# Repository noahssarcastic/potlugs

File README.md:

# potlugs
16mm panel-mount potentiometer wiring adaptor board.

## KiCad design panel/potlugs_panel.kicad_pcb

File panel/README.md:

# potlugs_panel

## Panelize (kikit)

```
kikit panelize ^
    --layout "grid; rows: 6; cols: 4; space: 2mm; rotation: 90deg" ^
    --tabs "fixed; width: 3mm; vcount: 1" ^
    --cuts "mousebites; drill: 0.5mm; spacing: 1mm; offset: 0.2mm; prolong: 0.5mm" ^
    --framing "frame; width: 5mm; space: 3mm; mintotalheight: 75mm; mintotalwidth: 75mm" ^
    --post "millradius: 1mm" ^
    "C:\Users\Noah\git\potlugs\potlugs.kicad_pcb" "C:\Users\Noah\git\potlugs\panel\potlugs_panel.kicad_pcb"
```

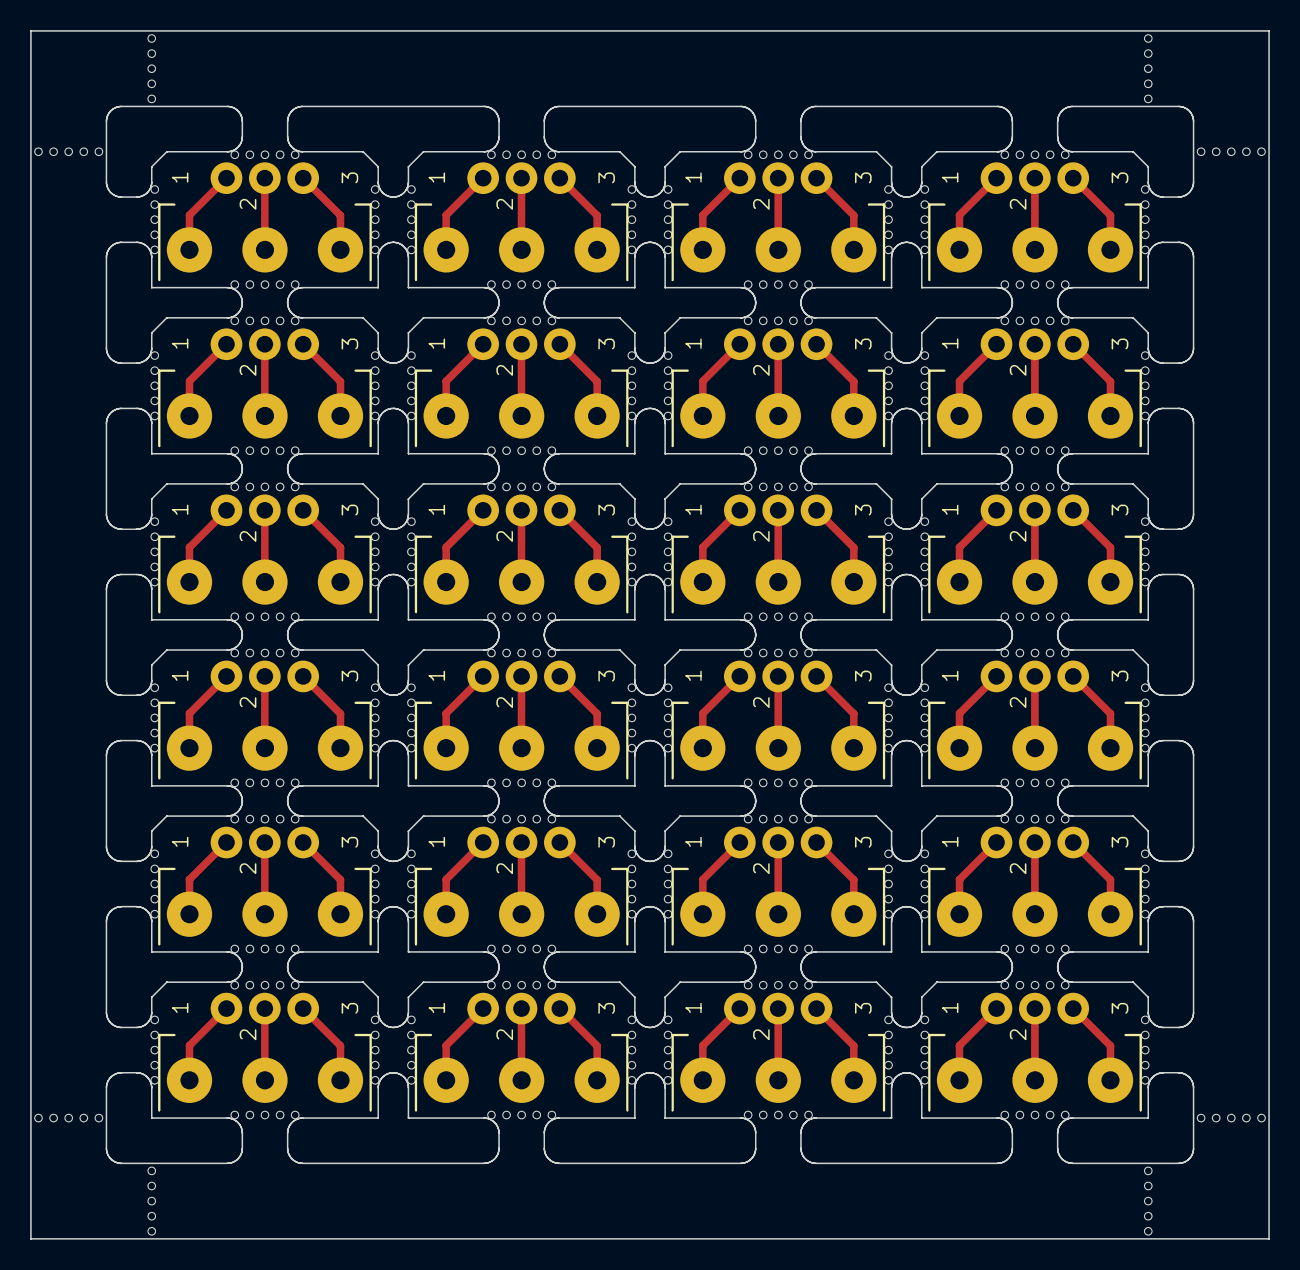
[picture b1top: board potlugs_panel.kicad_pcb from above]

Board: 2 copper layers, 82.0 x 80.0 mm, 568 parts (0 on the bottom side), 72 nets.

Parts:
J1, J1#2, J1#3, J1#4, J1#5, J1#6, J1#7, J1#8, J1#9, J1#10, J1#11, J1#12, J1#13, J1#14, J1#15, J1#16, J1#17, J1#18, J1#19, J1#20, J1#21, J1#22, J1#23, J1#24: 640456-3; PinHeader_1x3_P2.54_Drill1.1mm
KiKit_MB_1_1, KiKit_MB_1_2, KiKit_MB_1_3, KiKit_MB_1_4, KiKit_MB_1_5, KiKit_MB_2_1, KiKit_MB_2_2, KiKit_MB_2_3, KiKit_MB_2_4, KiKit_MB_2_5, KiKit_MB_3_1, KiKit_MB_3_2, KiKit_MB_3_3, KiKit_MB_3_4, KiKit_MB_3_5, KiKit_MB_4_1, KiKit_MB_4_2, KiKit_MB_4_3, KiKit_MB_4_4, KiKit_MB_4_5, KiKit_MB_5_1, KiKit_MB_5_2, KiKit_MB_5_3, KiKit_MB_5_4, KiKit_MB_5_5, KiKit_MB_6_1, KiKit_MB_6_2, KiKit_MB_6_3, KiKit_MB_6_4, KiKit_MB_6_5, KiKit_MB_7_1, KiKit_MB_7_2, KiKit_MB_7_3, KiKit_MB_7_4, KiKit_MB_7_5, KiKit_MB_8_1, KiKit_MB_8_2, KiKit_MB_8_3, KiKit_MB_8_4, KiKit_MB_8_5, KiKit_MB_9_1, KiKit_MB_9_2, KiKit_MB_9_3, KiKit_MB_9_4, KiKit_MB_9_5, KiKit_MB_10_1, KiKit_MB_10_2, KiKit_MB_10_3, KiKit_MB_10_4, KiKit_MB_10_5, KiKit_MB_11_1, KiKit_MB_11_2, KiKit_MB_11_3, KiKit_MB_11_4, KiKit_MB_11_5, KiKit_MB_12_1, KiKit_MB_12_2, KiKit_MB_12_3, KiKit_MB_12_4, KiKit_MB_12_5, KiKit_MB_13_1, KiKit_MB_13_2, KiKit_MB_13_3, KiKit_MB_13_4, KiKit_MB_13_5, KiKit_MB_14_1, KiKit_MB_14_2, KiKit_MB_14_3, KiKit_MB_14_4, KiKit_MB_14_5, KiKit_MB_15_1, KiKit_MB_15_2, KiKit_MB_15_3, KiKit_MB_15_4, KiKit_MB_15_5, KiKit_MB_16_1, KiKit_MB_16_2, KiKit_MB_16_3, KiKit_MB_16_4, KiKit_MB_16_5, KiKit_MB_17_1, KiKit_MB_17_2, KiKit_MB_17_3, KiKit_MB_17_4, KiKit_MB_17_5, KiKit_MB_18_1, KiKit_MB_18_2, KiKit_MB_18_3, KiKit_MB_18_4, KiKit_MB_18_5, KiKit_MB_19_1, KiKit_MB_19_2, KiKit_MB_19_3, KiKit_MB_19_4, KiKit_MB_19_5, KiKit_MB_20_1, KiKit_MB_20_2, KiKit_MB_20_3, KiKit_MB_20_4, KiKit_MB_20_5, KiKit_MB_21_1, KiKit_MB_21_2, KiKit_MB_21_3, KiKit_MB_21_4, KiKit_MB_21_5, KiKit_MB_22_1, KiKit_MB_22_2, KiKit_MB_22_3, KiKit_MB_22_4, KiKit_MB_22_5, KiKit_MB_23_1, KiKit_MB_23_2, KiKit_MB_23_3, KiKit_MB_23_4, KiKit_MB_23_5, KiKit_MB_24_1, KiKit_MB_24_2, KiKit_MB_24_3, KiKit_MB_24_4, KiKit_MB_24_5, KiKit_MB_25_1, KiKit_MB_25_2, KiKit_MB_25_3, KiKit_MB_25_4, KiKit_MB_25_5, KiKit_MB_26_1, KiKit_MB_26_2, KiKit_MB_26_3, KiKit_MB_26_4, KiKit_MB_26_5, KiKit_MB_27_1, KiKit_MB_27_2, KiKit_MB_27_3, KiKit_MB_27_4, KiKit_MB_27_5, KiKit_MB_28_1, KiKit_MB_28_2, KiKit_MB_28_3, KiKit_MB_28_4, KiKit_MB_28_5, KiKit_MB_29_1, KiKit_MB_29_2, KiKit_MB_29_3, KiKit_MB_29_4, KiKit_MB_29_5, KiKit_MB_30_1, KiKit_MB_30_2, KiKit_MB_30_3, KiKit_MB_30_4, KiKit_MB_30_5, KiKit_MB_31_1, KiKit_MB_31_2, KiKit_MB_31_3, KiKit_MB_31_4, KiKit_MB_31_5, KiKit_MB_32_1, KiKit_MB_32_2, KiKit_MB_32_3, KiKit_MB_32_4, KiKit_MB_32_5, KiKit_MB_33_1, KiKit_MB_33_2, KiKit_MB_33_3, KiKit_MB_33_4, KiKit_MB_33_5, KiKit_MB_34_1, KiKit_MB_34_2, KiKit_MB_34_3, KiKit_MB_34_4, KiKit_MB_34_5, KiKit_MB_35_1, KiKit_MB_35_2, KiKit_MB_35_3, KiKit_MB_35_4, KiKit_MB_35_5, KiKit_MB_36_1, KiKit_MB_36_2, KiKit_MB_36_3, KiKit_MB_36_4, KiKit_MB_36_5, KiKit_MB_37_1, KiKit_MB_37_2, KiKit_MB_37_3, KiKit_MB_37_4, KiKit_MB_37_5, KiKit_MB_38_1, KiKit_MB_38_2, KiKit_MB_38_3, KiKit_MB_38_4, KiKit_MB_38_5, KiKit_MB_39_1, KiKit_MB_39_2, KiKit_MB_39_3, KiKit_MB_39_4, KiKit_MB_39_5, KiKit_MB_40_1, KiKit_MB_40_2, KiKit_MB_40_3, KiKit_MB_40_4, KiKit_MB_40_5, KiKit_MB_41_1, KiKit_MB_41_2, KiKit_MB_41_3, KiKit_MB_41_4, KiKit_MB_41_5, KiKit_MB_42_1, KiKit_MB_42_2, KiKit_MB_42_3, KiKit_MB_42_4, KiKit_MB_42_5, KiKit_MB_43_1, KiKit_MB_43_2, KiKit_MB_43_3, KiKit_MB_43_4, KiKit_MB_43_5, KiKit_MB_44_1, KiKit_MB_44_2, KiKit_MB_44_3, KiKit_MB_44_4, KiKit_MB_44_5, KiKit_MB_45_1, KiKit_MB_45_2, KiKit_MB_45_3, KiKit_MB_45_4, KiKit_MB_45_5, KiKit_MB_46_1, KiKit_MB_46_2, KiKit_MB_46_3, KiKit_MB_46_4, KiKit_MB_46_5, KiKit_MB_47_1, KiKit_MB_47_2, KiKit_MB_47_3, KiKit_MB_47_4, KiKit_MB_47_5, KiKit_MB_48_1, KiKit_MB_48_2, KiKit_MB_48_3, KiKit_MB_48_4, KiKit_MB_48_5, KiKit_MB_49_1, KiKit_MB_49_2, KiKit_MB_49_3, KiKit_MB_49_4, KiKit_MB_49_5, KiKit_MB_50_1, KiKit_MB_50_2, KiKit_MB_50_3, KiKit_MB_50_4, KiKit_MB_50_5, KiKit_MB_51_1, KiKit_MB_51_2, KiKit_MB_51_3, KiKit_MB_51_4, KiKit_MB_51_5, KiKit_MB_52_1, KiKit_MB_52_2, KiKit_MB_52_3, KiKit_MB_52_4, KiKit_MB_52_5, KiKit_MB_53_1, KiKit_MB_53_2, KiKit_MB_53_3, KiKit_MB_53_4, KiKit_MB_53_5, KiKit_MB_54_1, KiKit_MB_54_2, KiKit_MB_54_3, KiKit_MB_54_4, KiKit_MB_54_5, KiKit_MB_55_1, KiKit_MB_55_2, KiKit_MB_55_3, KiKit_MB_55_4, KiKit_MB_55_5, KiKit_MB_56_1, KiKit_MB_56_2, KiKit_MB_56_3, KiKit_MB_56_4, KiKit_MB_56_5, KiKit_MB_57_1, KiKit_MB_57_2, KiKit_MB_57_3, KiKit_MB_57_4, KiKit_MB_57_5, KiKit_MB_58_1, KiKit_MB_58_2, KiKit_MB_58_3, KiKit_MB_58_4, KiKit_MB_58_5, KiKit_MB_59_1, KiKit_MB_59_2, KiKit_MB_59_3, KiKit_MB_59_4, KiKit_MB_59_5, KiKit_MB_60_1, KiKit_MB_60_2, KiKit_MB_60_3, KiKit_MB_60_4, KiKit_MB_60_5, KiKit_MB_61_1, KiKit_MB_61_2, KiKit_MB_61_3, KiKit_MB_61_4, KiKit_MB_61_5, KiKit_MB_62_1, KiKit_MB_62_2, KiKit_MB_62_3, KiKit_MB_62_4, KiKit_MB_62_5, KiKit_MB_63_1, KiKit_MB_63_2, KiKit_MB_63_3, KiKit_MB_63_4, KiKit_MB_63_5, KiKit_MB_64_1, KiKit_MB_64_2, KiKit_MB_64_3, KiKit_MB_64_4, KiKit_MB_64_5, KiKit_MB_65_1, KiKit_MB_65_2, KiKit_MB_65_3, KiKit_MB_65_4, KiKit_MB_65_5, KiKit_MB_66_1, KiKit_MB_66_2, KiKit_MB_66_3, KiKit_MB_66_4, KiKit_MB_66_5, KiKit_MB_67_1, KiKit_MB_67_2, KiKit_MB_67_3, KiKit_MB_67_4, KiKit_MB_67_5, KiKit_MB_68_1, KiKit_MB_68_2, KiKit_MB_68_3, KiKit_MB_68_4, KiKit_MB_68_5, KiKit_MB_69_1, KiKit_MB_69_2, KiKit_MB_69_3, KiKit_MB_69_4, KiKit_MB_69_5, KiKit_MB_70_1, KiKit_MB_70_2, KiKit_MB_70_3, KiKit_MB_70_4, KiKit_MB_70_5, KiKit_MB_71_1, KiKit_MB_71_2, KiKit_MB_71_3, KiKit_MB_71_4, KiKit_MB_71_5, KiKit_MB_72_1, KiKit_MB_72_2, KiKit_MB_72_3, KiKit_MB_72_4, KiKit_MB_72_5, KiKit_MB_73_1, KiKit_MB_73_2, KiKit_MB_73_3, KiKit_MB_73_4, KiKit_MB_73_5, KiKit_MB_74_1, KiKit_MB_74_2, KiKit_MB_74_3, KiKit_MB_74_4, KiKit_MB_74_5, KiKit_MB_75_1, KiKit_MB_75_2, KiKit_MB_75_3, KiKit_MB_75_4, KiKit_MB_75_5, KiKit_MB_76_1, KiKit_MB_76_2, KiKit_MB_76_3, KiKit_MB_76_4, KiKit_MB_76_5, KiKit_MB_77_1, KiKit_MB_77_2, KiKit_MB_77_3, KiKit_MB_77_4, KiKit_MB_77_5, KiKit_MB_78_1, KiKit_MB_78_2, KiKit_MB_78_3, KiKit_MB_78_4, KiKit_MB_78_5, KiKit_MB_79_1, KiKit_MB_79_2, KiKit_MB_79_3, KiKit_MB_79_4, KiKit_MB_79_5, KiKit_MB_80_1, KiKit_MB_80_2, KiKit_MB_80_3, KiKit_MB_80_4, KiKit_MB_80_5, KiKit_MB_81_1, KiKit_MB_81_2, KiKit_MB_81_3, KiKit_MB_81_4, KiKit_MB_81_5, KiKit_MB_82_1, KiKit_MB_82_2, KiKit_MB_82_3, KiKit_MB_82_4, KiKit_MB_82_5, KiKit_MB_83_1, KiKit_MB_83_2, KiKit_MB_83_3, KiKit_MB_83_4, KiKit_MB_83_5, KiKit_MB_84_1, KiKit_MB_84_2, KiKit_MB_84_3, KiKit_MB_84_4, KiKit_MB_84_5, KiKit_MB_85_1, KiKit_MB_85_2, KiKit_MB_85_3, KiKit_MB_85_4, KiKit_MB_85_5, KiKit_MB_86_1, KiKit_MB_86_2, KiKit_MB_86_3, KiKit_MB_86_4, KiKit_MB_86_5, KiKit_MB_87_1, KiKit_MB_87_2, KiKit_MB_87_3, KiKit_MB_87_4, KiKit_MB_87_5, KiKit_MB_88_1, KiKit_MB_88_2, KiKit_MB_88_3, KiKit_MB_88_4, KiKit_MB_88_5, KiKit_MB_89_1, KiKit_MB_89_2, KiKit_MB_89_3, KiKit_MB_89_4, KiKit_MB_89_5, KiKit_MB_90_1, KiKit_MB_90_2, KiKit_MB_90_3, KiKit_MB_90_4, KiKit_MB_90_5, KiKit_MB_91_1, KiKit_MB_91_2, KiKit_MB_91_3, KiKit_MB_91_4, KiKit_MB_91_5, KiKit_MB_92_1, KiKit_MB_92_2, KiKit_MB_92_3, KiKit_MB_92_4, KiKit_MB_92_5, KiKit_MB_93_1, KiKit_MB_93_2, KiKit_MB_93_3, KiKit_MB_93_4, KiKit_MB_93_5, KiKit_MB_94_1, KiKit_MB_94_2, KiKit_MB_94_3, KiKit_MB_94_4, KiKit_MB_94_5, KiKit_MB_95_1, KiKit_MB_95_2, KiKit_MB_95_3, KiKit_MB_95_4, KiKit_MB_95_5, KiKit_MB_96_1, KiKit_MB_96_2, KiKit_MB_96_3, KiKit_MB_96_4, KiKit_MB_96_5, KiKit_MB_97_2, KiKit_MB_97_3, KiKit_MB_97_4, KiKit_MB_97_5, KiKit_MB_97_6, KiKit_MB_98_2, KiKit_MB_98_3, KiKit_MB_98_4, KiKit_MB_98_5, KiKit_MB_98_6, KiKit_MB_99_2, KiKit_MB_99_3, KiKit_MB_99_4, KiKit_MB_99_5, KiKit_MB_99_6, KiKit_MB_100_2, KiKit_MB_100_3, KiKit_MB_100_4, KiKit_MB_100_5, KiKit_MB_100_6, KiKit_MB_101_2, KiKit_MB_101_3, KiKit_MB_101_4, KiKit_MB_101_5, KiKit_MB_101_6, KiKit_MB_102_2, KiKit_MB_102_3, KiKit_MB_102_4, KiKit_MB_102_5, KiKit_MB_102_6, KiKit_MB_103_2, KiKit_MB_103_3, KiKit_MB_103_4, KiKit_MB_103_5, KiKit_MB_103_6, KiKit_MB_104_2, KiKit_MB_104_3, KiKit_MB_104_4, KiKit_MB_104_5, KiKit_MB_104_6: NPTH
RV1, RV1#2, RV1#3, RV1#4, RV1#5, RV1#6, RV1#7, RV1#8, RV1#9, RV1#10, RV1#11, RV1#12, RV1#13, RV1#14, RV1#15, RV1#16, RV1#17, RV1#18, RV1#19, RV1#20, RV1#21, RV1#22, RV1#23, RV1#24: R_Potentiometer; Potentiometer_Alps_RK163_Single_Horizontal

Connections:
Board_0-Net-(J1-Pad1): J1#20.1, RV1#15.1
Board_0-Net-(J1-Pad2): J1#20.2, RV1#15.2
Board_0-Net-(J1-Pad3): J1#20.3, RV1#15.3
Board_1-Net-(J1-Pad1): J1#5.1, RV1#12.1
Board_1-Net-(J1-Pad2): J1#5.2, RV1#12.2
Board_1-Net-(J1-Pad3): J1#5.3, RV1#12.3
Board_2-Net-(J1-Pad1): J1#12.1, RV1#14.1
Board_2-Net-(J1-Pad2): J1#12.2, RV1#14.2
Board_2-Net-(J1-Pad3): J1#12.3, RV1#14.3
Board_3-Net-(J1-Pad1): J1#3.1, RV1#3.1
Board_3-Net-(J1-Pad2): J1#3.2, RV1#3.2
Board_3-Net-(J1-Pad3): J1#3.3, RV1#3.3
Board_4-Net-(J1-Pad1): J1#19.1, RV1#16.1
Board_4-Net-(J1-Pad2): J1#19.2, RV1#16.2
Board_4-Net-(J1-Pad3): J1#19.3, RV1#16.3
Board_5-Net-(J1-Pad1): J1#15.1, RV1#10.1
Board_5-Net-(J1-Pad2): J1#15.2, RV1#10.2
Board_5-Net-(J1-Pad3): J1#15.3, RV1#10.3
Board_6-Net-(J1-Pad1): J1#9.1, RV1#9.1
Board_6-Net-(J1-Pad2): J1#9.2, RV1#9.2
Board_6-Net-(J1-Pad3): J1#9.3, RV1#9.3
Board_7-Net-(J1-Pad1): J1#18.1, RV1#7.1
Board_7-Net-(J1-Pad2): J1#18.2, RV1#7.2
Board_7-Net-(J1-Pad3): J1#18.3, RV1#7.3
Board_8-Net-(J1-Pad1): J1#22.1, RV1#22.1
Board_8-Net-(J1-Pad2): J1#22.2, RV1#22.2
Board_8-Net-(J1-Pad3): J1#22.3, RV1#22.3
Board_9-Net-(J1-Pad1): J1#24.1, RV1.1
Board_9-Net-(J1-Pad2): J1#24.2, RV1.2
Board_9-Net-(J1-Pad3): J1#24.3, RV1.3
Board_10-Net-(J1-Pad1): J1#14.1, RV1#18.1
Board_10-Net-(J1-Pad2): J1#14.2, RV1#18.2
Board_10-Net-(J1-Pad3): J1#14.3, RV1#18.3
Board_11-Net-(J1-Pad1): J1#6.1, RV1#5.1
Board_11-Net-(J1-Pad2): J1#6.2, RV1#5.2
Board_11-Net-(J1-Pad3): J1#6.3, RV1#5.3
Board_12-Net-(J1-Pad1): J1#2.1, RV1#23.1
Board_12-Net-(J1-Pad2): J1#2.2, RV1#23.2
Board_12-Net-(J1-Pad3): J1#2.3, RV1#23.3
Board_13-Net-(J1-Pad1): J1#21.1, RV1#24.1
Board_13-Net-(J1-Pad2): J1#21.2, RV1#24.2
Board_13-Net-(J1-Pad3): J1#21.3, RV1#24.3
Board_14-Net-(J1-Pad1): J1#17.1, RV1#2.1
Board_14-Net-(J1-Pad2): J1#17.2, RV1#2.2
Board_14-Net-(J1-Pad3): J1#17.3, RV1#2.3
Board_15-Net-(J1-Pad1): J1#7.1, RV1#8.1
Board_15-Net-(J1-Pad2): J1#7.2, RV1#8.2
Board_15-Net-(J1-Pad3): J1#7.3, RV1#8.3
Board_16-Net-(J1-Pad1): J1#13.1, RV1#4.1
Board_16-Net-(J1-Pad2): J1#13.2, RV1#4.2
Board_16-Net-(J1-Pad3): J1#13.3, RV1#4.3
Board_17-Net-(J1-Pad1): J1#16.1, RV1#20.1
Board_17-Net-(J1-Pad2): J1#16.2, RV1#20.2
Board_17-Net-(J1-Pad3): J1#16.3, RV1#20.3
Board_18-Net-(J1-Pad1): J1#11.1, RV1#6.1
Board_18-Net-(J1-Pad2): J1#11.2, RV1#6.2
Board_18-Net-(J1-Pad3): J1#11.3, RV1#6.3
Board_19-Net-(J1-Pad1): J1#23.1, RV1#11.1
Board_19-Net-(J1-Pad2): J1#23.2, RV1#11.2
Board_19-Net-(J1-Pad3): J1#23.3, RV1#11.3
Board_20-Net-(J1-Pad1): J1#4.1, RV1#21.1
Board_20-Net-(J1-Pad2): J1#4.2, RV1#21.2
Board_20-Net-(J1-Pad3): J1#4.3, RV1#21.3
Board_21-Net-(J1-Pad1): J1.1, RV1#13.1
Board_21-Net-(J1-Pad2): J1.2, RV1#13.2
Board_21-Net-(J1-Pad3): J1.3, RV1#13.3
Board_22-Net-(J1-Pad1): J1#10.1, RV1#17.1
Board_22-Net-(J1-Pad2): J1#10.2, RV1#17.2
Board_22-Net-(J1-Pad3): J1#10.3, RV1#17.3
Board_23-Net-(J1-Pad1): J1#8.1, RV1#19.1
Board_23-Net-(J1-Pad2): J1#8.2, RV1#19.2
Board_23-Net-(J1-Pad3): J1#8.3, RV1#19.3

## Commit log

2026-02-27 Add schematic and layout for v1.0
2026-03-08 Make board bigger and remove bevels.
2026-03-09 Revert "Make board bigger and remove bevels."
    This reverts commit c6e11588c159b63a6cef385ffa4c164769ff8ee9.
2026-03-09 Add misc management files.
2026-03-09 Add panelized pcb layout.
2026-03-10 Update panel layout for cost savings.
